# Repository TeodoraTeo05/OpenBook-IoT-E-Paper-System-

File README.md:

# OpenBook

## General Description

OpenBook is a portable e-book reader device based on the ESP32-C6. The device features an e-paper screen, control buttons, an environmental sensor, a real-time clock, and the ability to be powered by a Li-Po battery, designed as an energy-efficient and scalable system.
---

#### 1 Block Diagram

---
## 2 BOM (Bill of Materials)

| Part | Device | Datasheet |
|------|--------|-----------|
| CHG_LED | ADAFRUIT_LEDCHIP-LED0603 | [ADAFRUIT_LEDCHIP-LED0603](https://www.snapeda.com/parts/KP-1608SURCK/Kingbright/view-part/?ref=search&t=LED%200603) |
| SJ1 | SJ | [SJ](https://grabcad.com/library/solder-jumpers-1) |
| EPD_C5 | EAGLE-LTSPICE_CC0402 | [EAGLE-LTSPICE_CC0402](https://www.snapeda.com/parts/PGB1010603MR/Littelfuse/view-part/?ref=eda) |
| R3 | ESP32_WROVER_EAGLE-LTSPICE_RR0402 | (https://componentsearchengine.com/part-view/R0402%201%25%20100%20K%20(RC0402FR-07100KL)/YAGEO) |
| R1_PWRUSB | ESP32_WROVER_EAGLE-LTSPICE_RR0402 | (https://componentsearchengine.com/part-view/R0402%201%25%20100%20K%20(RC0402FR-07100KL) |
| C4_USB | EAGLE-LTSPICE_CC0402 | [EAGLE-LTSPICE_CC0402](https://componentsearchengine.com/part-view/CC0402MRX5R5BB106/YAGEO) |
| C1, C2, C6, C8, C9, C10, C_DELAY | ESP32_WROVER_EAGLE-LTSPICE_CC0402 | [ESP32_WROVER_EAGLE-LTSPICE_CC0402](https://componentsearchengine.com/part-view/CC0402MRX5R5BB106/YAGEO) |
| C3 | RCL_CPOL-EUCT3528 | [RCL_CPOL-EUCT3528](https://componentsearchengine.com/part-view/CC0402MRX5R5BB106/YAGEO) |
| R1, R1_PINH, R1_PINH1, R2_PINH, R2_PINH1, R4, R5, R6, R7, R8, R9, R10, R_BOOT, R_CHANGE, R_CL1, R_RESET | ESP32_WROVER_EAGLE-LTSPICE_RR0402 | [ESP32_WROVER_EAGLE-LTSPICE_RR0402](https://componentsearchengine.com/part-view/R0402%201%25%20100%20K%20(RC0402FR-07100KL)/YAGEO) |
| C7 | ESP32_WROVER_EAGLE-LTSPICE_CC0402 | [ESP32_WROVER_EAGLE-LTSPICE_CC0402](https://componentsearchengine.com/part-view/CC0402MRX5R5BB106/YAGEO) |
| J4 | 112A-TAAR-R03_ATTEND | [112A-TAAR-R03_ATTEND](https://store.comet.srl.ro/Catalogue/Product/43497/) |
| R_CAPACITOR | ESP32_WROVER_EAGLE-LTSPICE_RR0402 | [ESP32_WROVER_EAGLE-LTSPICE_RR0402](https://componentsearchengine.com/part-view/R0402%201%25%20100%20K%20(RC0402FR-07100KL)/YAGEO) |
| C5 | ESP32_WROVER_EAGLE-LTSPICE_CC0402 | [ESP32_WROVER_EAGLE-LTSPICE_CC0402](https://componentsearchengine.com/part-view/CC0402MRX5R5BB106/YAGEO) |
| EPD_C6, EPD_C7, EPD_C8, EPD_C9, EPD_C10, EPD_C11, EPD_C12 | EAGLE-LTSPICE_CC0402 | [EAGLE-LTSPICE_CC0402](https://componentsearchengine.com/part-view/CC0402MRX5R5BB106/YAGEO) |
| EPD_C1, EPD_C2 | ESP32_WROVER_EAGLE-LTSPICE_CC0402 | [ESP32_WROVER_EAGLE-LTSPICE_CC0402](https://componentsearchengine.com/part-view/CC0402MRX5R5BB106/YAGEO) |
| R2 | ESP32_WROVER_EAGLE-LTSPICE_RR0402 | [ESP32_WROVER_EAGLE-LTSPICE_RR0402](https://componentsearchengine.com/part-view/R0402%201%25%20100%20K%20(RC0402FR-07100KL)/YAGEO) |
| R1_BAT | ESP32_WROVER_EAGLE-LTSPICE_RR0402 | [ESP32_WROVER_EAGLE-LTSPICE_RR0402](https://componentsearchengine.com/part-view/R0402%201%25%20100%20K%20(RC0402FR-07100KL)/YAGEO) |
| Q1, Q2 | ESP32_WROVER_SPARKFUN-DISCRETESEMI_MOSFET_PCH-DMG2305UX-7 | [ESP32_WROVER_SPARKFUN-DISCRETESEMI_MOSFET_PCH-DMG2305UX-7](https://componentsearchengine.com/part-view/DMG2305UX-7/Diodes%20Incorporated) |
| R2_BAT | ESP32_WROVER_EAGLE-LTSPICE_RR0402 | [ESP32_WROVER_EAGLE-LTSPICE_RR0402](https://componentsearchengine.com/part-view/R0402%201%25%20100%20K%20(RC0402FR-07100KL)/YAGEO) |
| C5_USB | EAGLE-LTSPICE_CC0402 | [EAGLE-LTSPICE_CC0402](https://componentsearchengine.com/part-view/CC0402MRX5R5BB106/YAGEO) |
| C1_BAT, C1_BAT1, C1_BAT2, C2_BAT | ESP32_WROVER_EAGLE-LTSPICE_CC0402 | [ESP32_WROVER_EAGLE-LTSPICE_CC0402](https://componentsearchengine.com/part-view/CC0402MRX5R5BB106/YAGEO) |
| C4 | ESP32_WROVER_EAGLE-LTSPICE_CC0402 | [ESP32_WROVER_EAGLE-LTSPICE_CC0402](https://componentsearchengine.com/part-view/CC0402MRX5R5BB106/YAGEO) |
| R2-USB, R2-USB1 | ESP32_WROVER_EAGLE-LTSPICE_RR0402 | [ESP32_WROVER_EAGLE-LTSPICE_RR0402](https://componentsearchengine.com/part-view/R0402%201%25%20100%20K%20(RC0402FR-07100KL)/YAGEO) |
| L1 | 744043680IND_4828-WE-TPC_WRE | [744043680IND_4828-WE-TPC_WRE](https://eu.mouser.com/ProductDetail/Wurth-Elektronik/744043680?qs=PGXP4M47uW6VkZq%252BkzjrHA%3D%3D) |
| IC1 | BD5229G-TR | [BD5229G-TR](https://componentsearchengine.com/part-view/BD5229G-TR/ROHM%20Semiconductor) |
| SENSOR2 | ESP32_WROVER_BME680_BME680 | [ESP32_WROVER_BME680_BME680](https://www.snapeda.com/parts/BME680/Bosch/view-part/?welcome=home) |
| BUTTON_CUSYOMV1 | BUTTON_CUSYOMV1 | [BUTTON_CUSYOMV1](https://industry.panasonic.com/global/en/products/control/switch/light-touch/number/evqpuj02k) |
| C10_SUPERCAP | CPH3225A | [CPH3225A](https://www.snapeda.com/parts/CPH3225A/Seiko+Instruments/view-part/?ref=snap) |
| U3 | DS3231SN# | [DS3231SN#](https://www.snapeda.com/parts/DS3231SN%23/Analog+Devices/view-part/?ref=snap) |
| U2 | ESP32-C6-WROOM-1-N8 | [ESP32-C6-WROOM-1-N8](https://www.snapeda.com/parts/ESP32-C6-WROOM-1-N8/Espressif+Systems/view-part/?ref=eda) |
| PFMF.050.1 | ESP32C6_VARISTORCN1812 | [ESP32C6_VARISTORCN1812](https://www.mouser.co.uk/ProductDetail/EPCOS-TDK/B72520T0350K062?qs=dEfas%2FXlABIszF52uu7vrg%3D%3D) |
| D2, D7 | ESP32_WROVER_AVX---SD0805S020S1R0_AVX_SD0805S020S1R0_0_0AVX_SD0805S020S1R0_0_0 | [ESP32_WROVER_AVX---SD0805S020S1R0_AVX_SD0805S020S1R0_0_0AVX_SD0805S020S1R0_0_0](https://eu.mouser.com/ProductDetail/KYOCERA-AVX/SD0805S020S1R0?qs=jCA%252BPfw4LHbpkAoSnwrdjw%3D%3D) |
| U5 | ESP32_WROVER_SPARKFUN-IC-POWER_MCP73831 | [ESP32-C6-WROOM-1-N8](https://componentsearchengine.com/part-view/MCP73831T-2ATI%2FOT/Microchip) |
| J1 | FH34SRJ-24S-0.5SH_99_ | [FH34SRJ-24S-0.5SH_99_](https://componentsearchengine.com/part-view/XC6220A331MR-G/Torex) |
| U4 | MAX17048G+T10 | [MAX17048G+T10](https://www.snapeda.com/parts/MAX17048G+T10/Analog+Devices/view-part/?ref=snap) |
| D3, D4, D5 | MBR0530 | [MBR0530](https://www.snapeda.com/parts/MBR0530/Onsemi/view-part/?ref=snap) |
| D6, D8, D9, D10, D11, D12 | PGB1010603MR | [PGB1010603MR](https://www.snapeda.com/parts/PGB1010603MR/Littelfuse/view-part/?ref=snap) |
| J3 | QWIIC_CONNECTORJS-1MM | [QWIIC_CONNECTORJS-1MM](https://www.snapeda.com/parts/PRT-14417/SparkFun%20Electronics/view-part/?ref=search&t=qwiic) |
| J2 | SAMACSYS_PARTS_USB4110-GF-A | (https://componentsearchengine.com/part-view/USB4110-GF-A/GCT%20(GLOBAL%20CONNECTOR%20TECHNOLOGY) |
| Q3 | SI1308EDL-T1-GE3 | [SI1308EDL-T1-GE3](https://componentsearchengine.com/part-view/SI1308EDL-T1-GE3/Vishay) |
| TP1, TP2, TP3, TP4, TP5, TP6, TP7, TP8, TP9, TP10, TP11, TP12, TP13, TP14, TP15, TP16, TP17 | TPTP20R | [made by me] |
| D1 | USBLC6-2SC6Y | [USBLC6-2SC6Y](https://www.snapeda.com/parts/USBLC6-2SC6Y/STMicroelectronics/view-part/?ref=snap) |
| U1 | W25Q512JVEIQ | [W25Q512JVEIQ](https://www.snapeda.com/parts/W25Q512JVEIQ/Winbond+Electronics/view-part/?ref=snap) |
| IC4 | XC6220A331MR-G | [XC6220A331MR-G](https://componentsearchengine.com/part-view/XC6220A331MR-G/Torex) |

## 3. Hardware Functionality

The OpenBook project is an e-paper reader, powered by a LiPo battery and built around the ESP32-C3-WROOM microcontroller. 
The device collects environmental data (temperature, humidity, CO2, particles), saves them to a microSD card, and can display them on the e-paper screen.

### ESP32-C3-WROOM
- Main module with Wi-Fi/BLE connectivity, capable of communicating via SPI, I2C, and UART.
- Supply voltage: 3.3V, provided by an LDO.

### Power System
- **USB-C** is used for charging and USB communication.
- **MCP73832** manages the LiPo battery charging.
- **3.3V LDO** powers the ESP32 and the rest of the components at 3.3V.
- **5V DC/DC** generates 5V for sensors that require a higher voltage (PM and CO2).

### Sensors
- **BME680** - temperature, humidity, and gas sensor, communicates via I2C.
- **MH-Z19B** - CO2 sensor powered at 5V, communicates via UART.
- **PMSA003** - fine particle sensor (PM2.5), communicates via UART, 5V.

### Display
- 1.5" monochrome e-paper display with 200x200 px resolution.
- Shared SPI interface with the SD Card.

### SD Card
- Module for storing collected data or text files.
- SPI interface.

### Buttons
- 3 tactile buttons connected to GPIO for interface control (e.g., menu navigation, screen refresh).

### Estimated power consumption calculations (average values)

| Module | Voltage | Current (mA) | Estimated Consumption |
|--------|---------|--------------|-----------------------|
| ESP32-C3 | 3.3V | 80-150 | 0.3-0.5W |
| E-Ink Display | 3.3V | 10 (refresh) | 0.03W |
| BME680 | 3.3V | 2-3 | 0.01W |
| MH-Z19B | 5V | 40-50 | 0.25W |
| PMSA003 | 5V | 60-100 | 0.5W |
| SD Card | 3.3V | 10 | 0.03W |
| MCP73832 (charger) | 5V | 1000 (max) | only when charging |

**Deep sleep mode:** Total consumption under 1 mA. Ideal for a portable device.

## 4. ESP32-C3 Pinout

| ESP32-C3 Pin | Component | Reason / Signal |
|--------------|-----------|-----------------|
| GPIO1 (I2C SDA) | BME680 | I2C Communication |
| GPIO2 (I2C SCL) | BME680 | I2C Communication |
| GPIO3 (UART RX) | PMSA003 | UART RX PM sensor |
| GPIO4 (SPI CS SD)| SD Card | SD Card Chip Select |
| GPIO5 | E-Ink DC | Data/Command E-Ink |
| GPIO6 (SPI CLK) | E-Ink & SD | SPI Clock |
| GPIO7 (SPI MOSI) | E-Ink & SD | SPI Data |
| GPIO8 (GPIO) | Button 1 | Menu control / page flip |
| GPIO9 (GPIO) | Button 2 | Menu control / page flip |
| GPIO10 (SPI CS) | E-Ink Display | e-paper Chip Select |
| GPIO11 (SPI CS) | External Flash (optional)| N/A |
| GPIO12 (USB D-) | USB | USB Communication |
| GPIO13 (USB D+) | USB | USB Communication |
| GPIO18 | MH-Z19B (UART TX) | UART for CO2 sensor |
| GPIO19 | Button 3 | Navigation / confirm |

## 5. Other relevant aspects

- The PCB design follows the recommendations for power traces (min 0.3mm) and signal traces (min 0.15mm).
- The ESP32-C3 antenna is placed towards the outside of the board, and the area underneath it is cut out.
- Decoupling capacitors are placed close to the VCC of the components.
- Solid ground plane on both layers and active via stitching.
- All passive components are SMD 0402.
- The layout is designed in Fusion360, aligned with the physical case dimensions.
- Rendered images of the device and case can be found in the `Images/` folder of this repository.

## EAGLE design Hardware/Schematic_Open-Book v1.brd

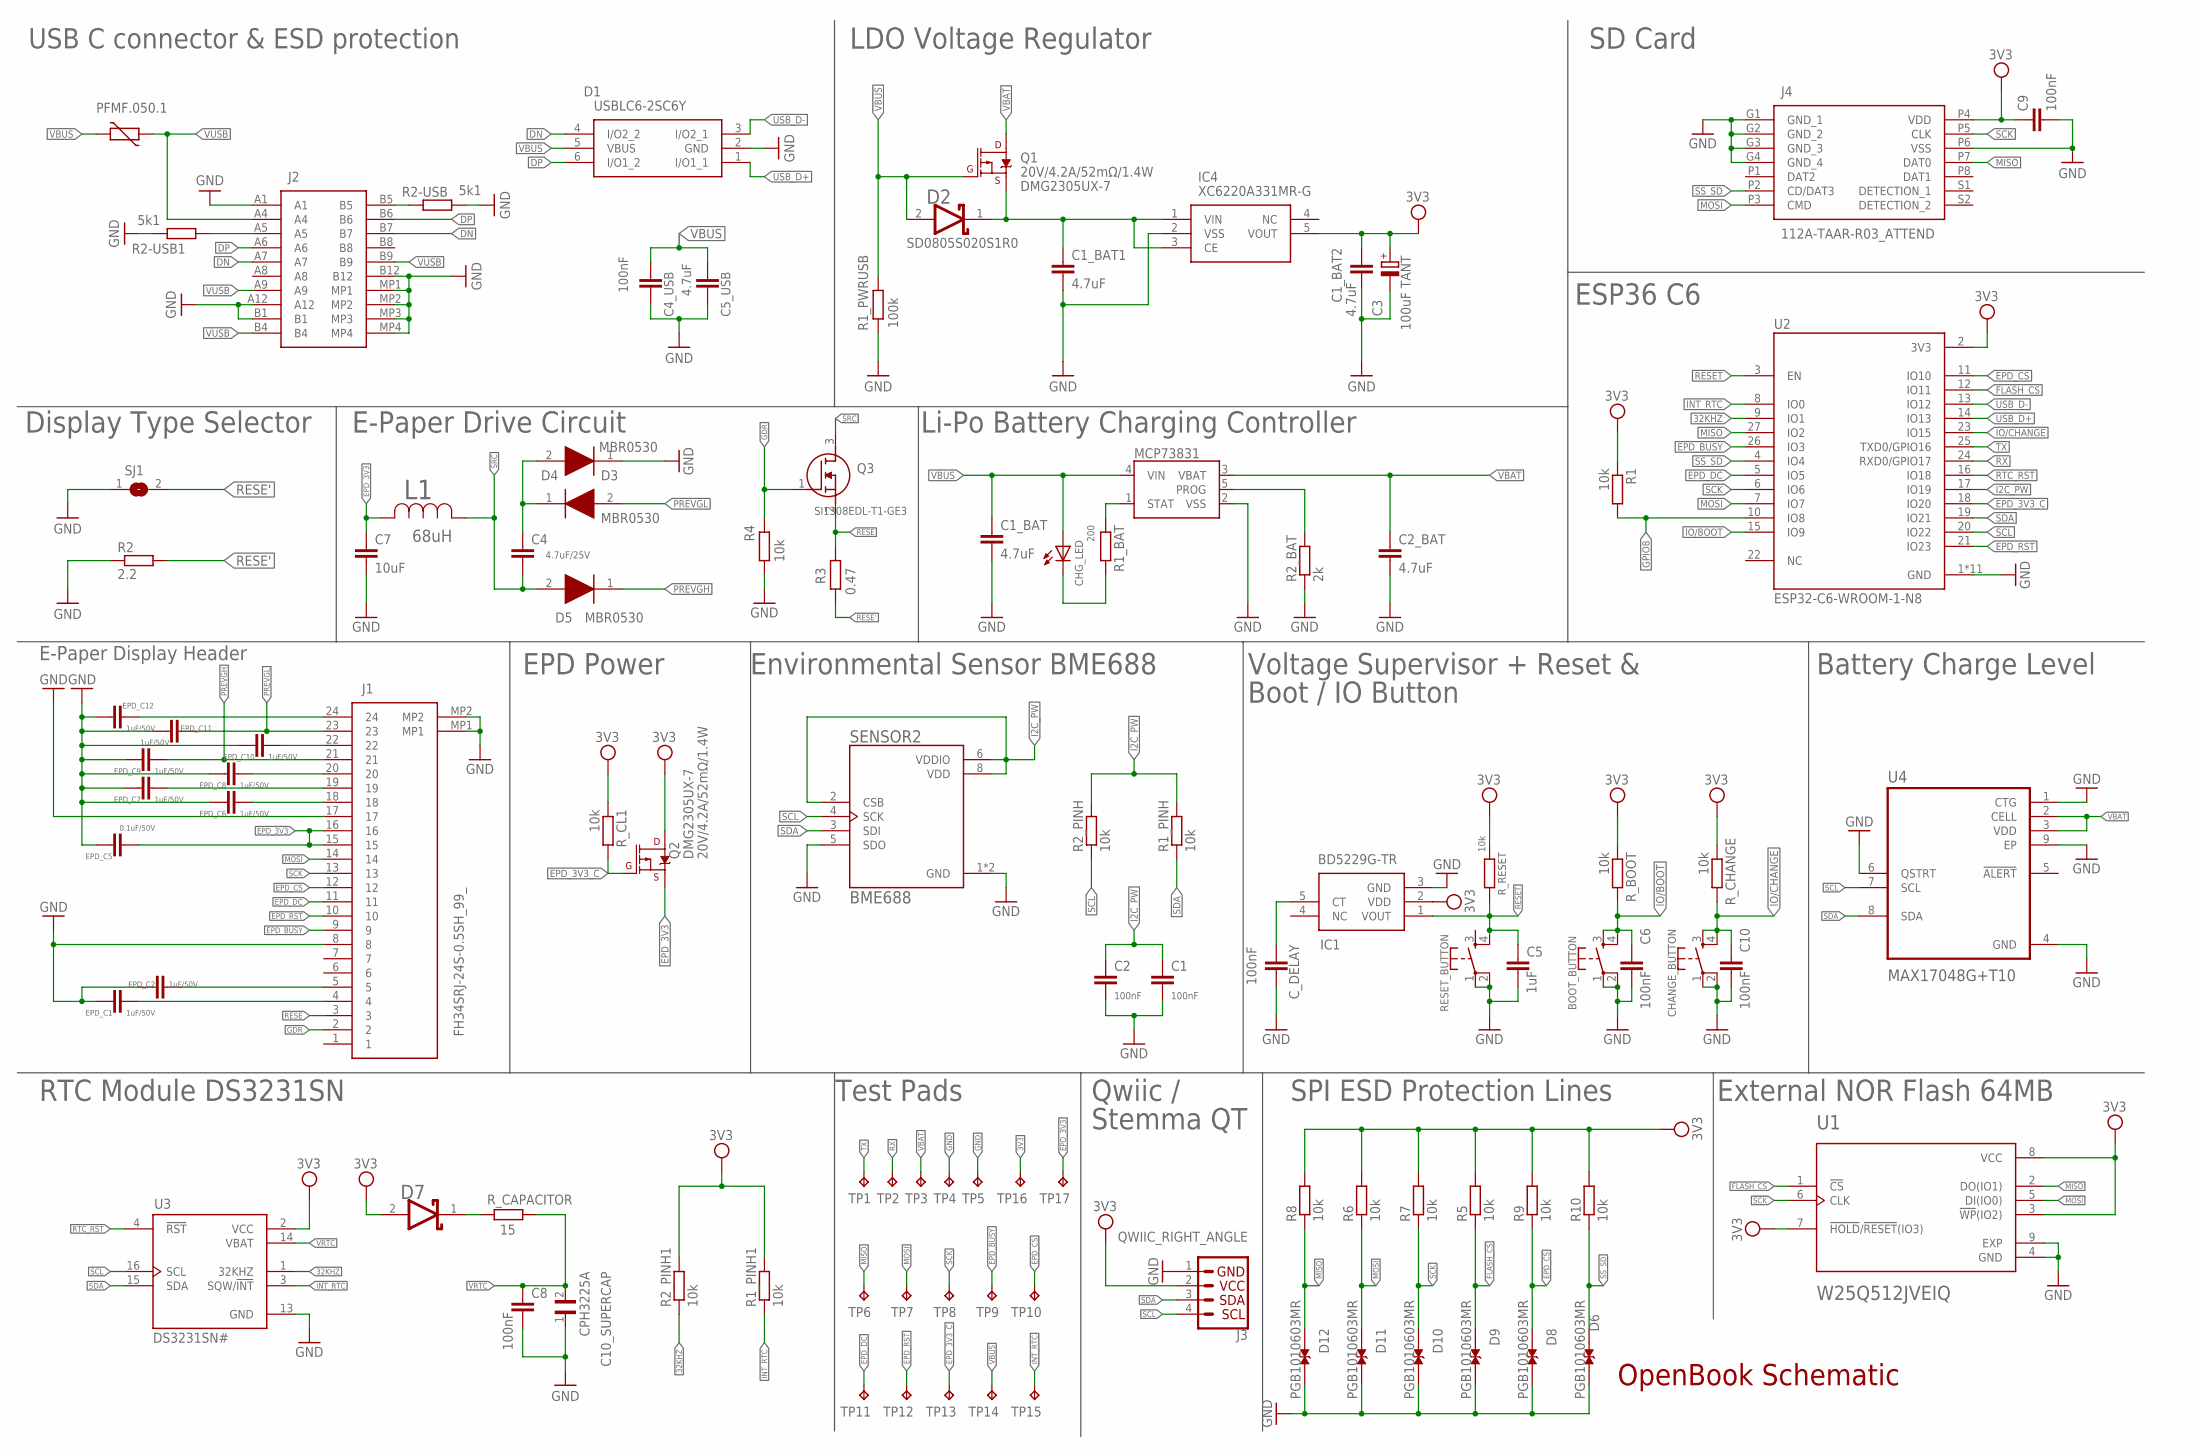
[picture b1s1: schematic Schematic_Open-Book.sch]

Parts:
BOOT_BUTTON: BOOT_BUTTON; MYBUTTON
C1, C2, C6, C8, C9, C10: 100nF; ESP32_WROVER_EAGLE-LTSPICE_C0402
C1_BAT, C1_BAT1, C1_BAT2, C2_BAT: 4.7uF; ESP32_WROVER_EAGLE-LTSPICE_C0402
C3: 100uF TANT; RCL_CT3528
C4: 4.7uF/25V; ESP32_WROVER_EAGLE-LTSPICE_C0402
C4_USB: 100nF; EAGLE-LTSPICE_C0402
C5: 1uF; ESP32_WROVER_EAGLE-LTSPICE_C0402
C5_USB: 4.7uF; EAGLE-LTSPICE_C0402
C7: 10uF; ESP32_WROVER_EAGLE-LTSPICE_C0402
C10_SUPERCAP: CPH3225A; CAPCP3225X100N
CHANGE_BUTTON: CHANGE_BUTTON; MYBUTTON
CHG_LED: ADAFRUIT_LEDCHIP-LED0603; ADAFRUIT_CHIP-LED0603
C_DELAY: 100nF; ESP32_WROVER_EAGLE-LTSPICE_C0402
D1: USBLC6-2SC6Y; SOT95P280X145-6N
D2, D7: ESP32_WROVER_AVX---SD0805S020S1R0_AVX_SD0805S020S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; ESP32_WROVER_AVX---SD0805S020S1R0_AVX_SD0805S020S1R0_0
D3, D4, D5: MBR0530; SOD3716X135N
D6, D8, D9, D10, D11, D12: PGB1010603MR; DIOC1608X36N
EPD_C1, EPD_C2: 1uF/50V; ESP32_WROVER_EAGLE-LTSPICE_C0402
EPD_C5: 0.1uF/50V; EAGLE-LTSPICE_C0402
EPD_C6, EPD_C7, EPD_C8, EPD_C9, EPD_C10, EPD_C11, EPD_C12: 1uF/50V; EAGLE-LTSPICE_C0402
IC1: BD5229G-TR; SOT95P280X125-5N
IC4: XC6220A331MR-G; SOT95P280X120-5N
J1: FH34SRJ-24S-0.5SH_99_; FH34SRJ24S05SH99
J2: SAMACSYS_PARTS_USB4110-GF-A; SAMACSYS_PARTS_USB4110GFA
J3: QWIIC_RIGHT_ANGLE; JST04_1MM_RA
J4: 112A-TAAR-R03_ATTEND; 112ATAARR03ATTEND
L1: 68uH; IND_4828-WE-TPC_WRE
MCP73831: ESP32_WROVER_SPARKFUN-IC-POWER_MCP73831; ESP32_WROVER_SPARKFUN-IC-POWER_SOT23-5
PFMF.050.1: ESP32C6_VARISTORCN1812; ESP32C6_VARISTOR_CT/CN1812
Q1, Q2: 20V/4.2A/52mΩ/1.4W; ESP32_WROVER_SPARKFUN-DISCRETESEMI_SOT23-3
Q3: SI1308EDL-T1-GE3; SOT65P210X110-3N
R1, R1_PINH, R1_PINH1, R2_PINH, R2_PINH1, R4, R5, R6, R7, R8, R9, R10: 10k; ESP32_WROVER_EAGLE-LTSPICE_R0402
R1_BAT: 200; ESP32_WROVER_EAGLE-LTSPICE_R0402
R1_PWRUSB: 100k; ESP32_WROVER_EAGLE-LTSPICE_R0402
R2: 2.2; ESP32_WROVER_EAGLE-LTSPICE_R0402
R2-USB, R2-USB1: 5k1; ESP32_WROVER_EAGLE-LTSPICE_R0402
R2_BAT: 2k; ESP32_WROVER_EAGLE-LTSPICE_R0402
R3: 0.47; ESP32_WROVER_EAGLE-LTSPICE_R0402
RESET_BUTTON: RESET_BUTTON; MYBUTTON
R_BOOT: 10k; ESP32_WROVER_EAGLE-LTSPICE_R0402
R_CAPACITOR: 15; ESP32_WROVER_EAGLE-LTSPICE_R0402
R_CHANGE: 10k; ESP32_WROVER_EAGLE-LTSPICE_R0402
R_CL1: 10k; ESP32_WROVER_EAGLE-LTSPICE_R0402
R_RESET: 10k; ESP32_WROVER_EAGLE-LTSPICE_R0402
SENSOR2: BME688; ESP32_WROVER_BME680_PSON80P300X300X100-8N
SJ1: SJ
TP1, TP2, TP3, TP4, TP5, TP6, TP7, TP8, TP9, TP10, TP11, TP12, TP13, TP14, TP15, TP16, TP17: TPTP20R; TP20R
U1: W25Q512JVEIQ; SON127P600X800X80-9N
U2: ESP32-C6-WROOM-1-N8; XCVR_ESP32-C6-WROOM-1-N8
U3: DS3231SN#; SOIC127P1032X265-16N
U4: MAX17048G+T10; SON50P200X200X80-9N

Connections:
3V3: C1_BAT2.1, C3.+, C9.1, D7.2 (ANODE), IC1.2 (VDD), IC4.5 (VOUT), J3.2, J4.P4 (VDD), Q2.3 (D), R1.1, R1_PINH1.2, R2_PINH1.2, R5.2, R6.2, R7.2, R8.2, R9.2, R10.2, R_BOOT.1, R_CHANGE.1, R_CL1.1, R_RESET.1, TP16.TP, U1.3 (!WP!(IO2)), U1.7 (!HOLD!/!RESET!(IO3)), U1.8 (VCC), U2.2 (3V3), U3.2 (VCC)
32KHZ: R2_PINH1.1, U2.9 (IO1), U3.1 (32KHZ)
DN: D1.4 (I/O2_2), J2.A7, J2.B7
DP: D1.6 (I/O1_2), J2.A6, J2.B6
EPD_3V3: C7.1, EPD_C5.1, J1.15, J1.16, L1.2, Q2.2 (S), TP17.TP
EPD_3V3_C: Q2.1 (G), R_CL1.2, TP13.TP, U2.18 (IO20)
EPD_BUSY: J1.9, TP9.TP, U2.26 (IO3)
EPD_CS: D8.1, J1.12, R9.1, TP10.TP, U2.11 (IO10)
EPD_DC: J1.11, TP11.TP, U2.5 (IO5)
EPD_RST: J1.10, TP12.TP, U2.21 (IO23)
FLASH_CS: D9.1, R5.1, U1.1 (!CS), U2.12 (IO11)
GDR: J1.2, Q3.1 (G), R4.1
GND: BOOT_BUTTON.1, BOOT_BUTTON.2, C1.2, C1_BAT.2, C1_BAT1.2, C1_BAT2.2, C2.2, C2_BAT.2, C3.-, C4_USB.2, C5.2, C5_USB.2, C6.2, C7.2, C8.2, C9.2, C10.2, C10_SUPERCAP.1, CHANGE_BUTTON.1, CHANGE_BUTTON.2, C_DELAY.2, D1.2 (GND), D4.1 (K), D6.2, D8.2, D9.2, D10.2, D11.2, D12.2, EPD_C1.2, EPD_C2.2, EPD_C5.2, EPD_C6.2, EPD_C7.2, EPD_C8.2, EPD_C9.2, EPD_C10.2, EPD_C11.2, EPD_C12.2, IC1.3 (GND), IC4.2 (VSS), J1.8, J1.17, J1.MP1, J1.MP2, J2.A1, J2.A12, J2.B1, J2.B12, J2.MP1, J2.MP2, J2.MP3, J2.MP4, J3.1, J4.G1 (GND_1), J4.G2 (GND_2), J4.G3 (GND_3), J4.G4 (GND_4), J4.P6 (VSS), MCP73831.2 (VSS), R1_PWRUSB.2, R2.1, R2-USB.2, R2-USB1.1, R2_BAT.1, R4.2, RESET_BUTTON.1, RESET_BUTTON.2, SENSOR2.1 (GND), SENSOR2.5 (SDO), SENSOR2.7 (GND), SJ1.1, TP4.TP, TP5.TP, U1.4 (GND), U1.9 (EXP), U2.1 (GND), U2.28 (GND), U2.29_1 (GND), U2.29_2 (GND), U2.29_3 (GND), U2.29_4 (GND), U2.29_5 (GND), U2.29_6 (GND), U2.29_7 (GND), U2.29_8 (GND), U2.29_9 (GND), U3.13 (GND), U4.1 (CTG), U4.4 (GND), U4.6 (QSTRT), U4.9 (EP)
GPIO8: R1.2, U2.10 (IO8)
I2C_PW: C1.1, C2.1, R1_PINH.2, R2_PINH.2, SENSOR2.2 (CSB), SENSOR2.6 (VDDIO), SENSOR2.8 (VDD), U2.17 (IO19)
INT_RTC: R1_PINH1.1, TP15.TP, U2.8 (IO0), U3.3 (SQW/!INT)
IO/BOOT: BOOT_BUTTON.3, BOOT_BUTTON.4, C6.1, R_BOOT.2, U2.15 (IO9)
IO/CHANGE: C10.1, CHANGE_BUTTON.3, CHANGE_BUTTON.4, R_CHANGE.2, U2.23 (IO15)
MISO: D12.1, J4.P7 (DAT0), R8.1, TP6.TP, U1.2 (DO(IO1)), U2.27 (IO2)
MOSI: D11.1, J1.14, J4.P3 (CMD), R6.1, TP7.TP, U1.5 (DI(IO0)), U2.7 (IO7)
unnamed: J2.B5, R2-USB.1
unnamed: J2.A5, R2-USB1.2
unnamed: C4.1, D3.1 (K), D4.2 (A)
unnamed: C1_BAT1.1, D2.1 (CATHODE), IC4.1 (VIN), IC4.3 (CE), Q1.2 (S)
unnamed: MCP73831.5 (PROG), R2_BAT.2
unnamed: CHG_LED.C, R1_BAT.2
unnamed: MCP73831.1 (STAT), R1_BAT.1
unnamed: C_DELAY.1, IC1.5 (CT)
unnamed: EPD_C2.1, J1.5
unnamed: EPD_C1.1, J1.4
unnamed: D7.1 (CATHODE), R_CAPACITOR.2
unnamed: EPD_C12.1, J1.24
unnamed: EPD_C10.1, J1.22
unnamed: EPD_C8.1, J1.20
unnamed: EPD_C7.1, J1.19
unnamed: EPD_C6.1, J1.18
PREVGH: D5.1 (K), EPD_C9.1, J1.21
PREVGL: D3.2 (A), EPD_C11.1, J1.23
RESE: J1.3, Q3.2 (S), R3.1
RESE': R2.2, R3.2, SJ1.2
RESET: C5.1, IC1.1 (VOUT), RESET_BUTTON.4, R_RESET.2, U2.3 (EN)
RTC_RST: U2.16 (IO18), U3.4 (!RST)
RX: TP2.TP, U2.24 (RXD0/GPIO17)
SCK: D10.1, J1.13, J4.P5 (CLK), R7.1, TP8.TP, U1.6 (CLK), U2.6 (IO6)
SCL: J3.4, R2_PINH.1, SENSOR2.4 (SCK), U2.20 (IO22), U3.16 (SCL), U4.7 (SCL)
SDA: J3.3, R1_PINH.1, SENSOR2.3 (SDI), U2.19 (IO21), U3.15 (SDA), U4.8 (SDA)
SRC: C4.2, D5.2 (A), L1.1, Q3.3 (D)
SS_SD: D6.1, J4.P2 (CD/DAT3), R10.1, U2.4 (IO4)
TX: TP1.TP, U2.25 (TXD0/GPIO16)
USB_D+: D1.1 (I/O1_1), U2.14 (IO13)
USB_D-: D1.3 (I/O2_1), U2.13 (IO12)
VBAT: C2_BAT.1, MCP73831.3 (VBAT), Q1.3 (D), TP3.TP, U4.2 (CELL), U4.3 (VDD)
VBUS: C1_BAT.1, C4_USB.1, C5_USB.1, CHG_LED.A, D1.5 (VBUS), D2.2 (ANODE), MCP73831.4 (VIN), PFMF.050.1.2, Q1.1 (G), R1_PWRUSB.1, TP14.TP
VRTC: C8.1, C10_SUPERCAP.2, R_CAPACITOR.1, U3.14 (VBAT)
VUSB: J2.A4, J2.A9, J2.B4, J2.B9, PFMF.050.1.1

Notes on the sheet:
USB C connector & ESD protection
LDO Voltage Regulator
SD0805S020S1R0
DMG2305UX-7
SD Card
Display Type Selector
E-Paper Drive Circuit
Li-Po Battery Charging Controller
ESP36 C6
E-Paper Display Header
EPD Power
Environmental Sensor BME688
Voltage Supervisor + Reset &
Boot / IO Button
Battery Charge Level
RTC Module DS3231SN
Test Pads
Qwiic /
Stemma QT
SPI ESD Protection Lines
External NOR Flash 64MB
OpenBook Schematic

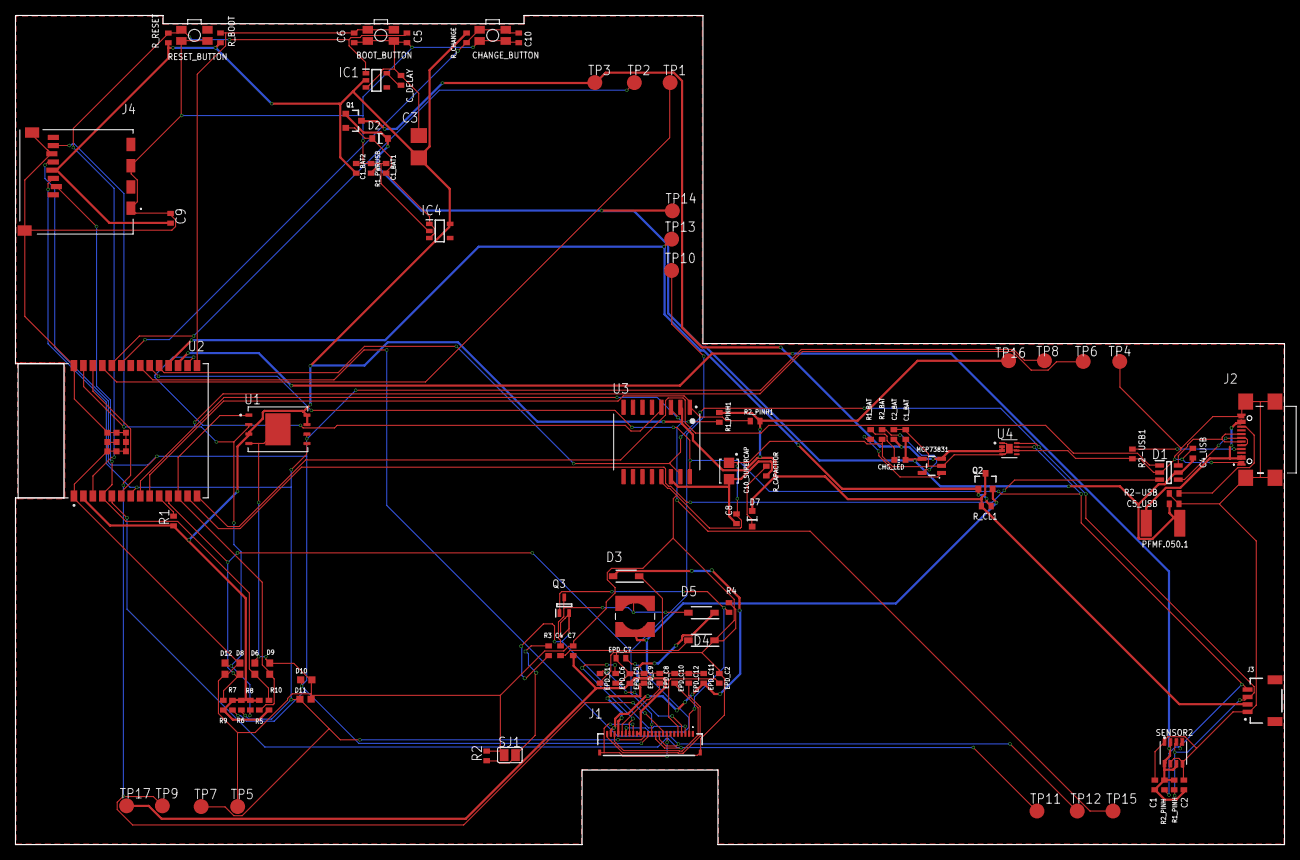
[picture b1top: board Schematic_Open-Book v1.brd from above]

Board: 2 copper layers, 170.2 x 111.2 mm, 103 parts (0 on the bottom side), 55 nets.

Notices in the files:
parts and their libraries:
COPYRIGHT: Copyright (C) 2024 Ultra Librarian. All rights reserved.
